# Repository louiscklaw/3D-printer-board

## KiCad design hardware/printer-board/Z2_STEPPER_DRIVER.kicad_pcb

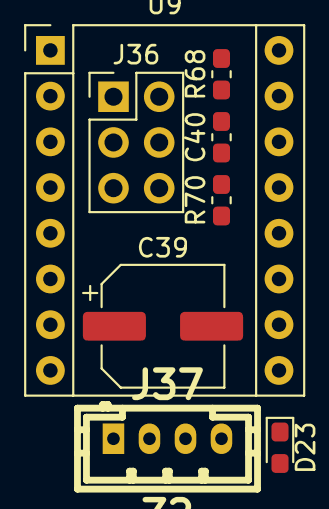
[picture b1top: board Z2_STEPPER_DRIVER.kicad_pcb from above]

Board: 2 copper layers, 9 parts (1 on the bottom side), 13 nets, no tracks yet.

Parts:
C39: CP100uf,25V; CP_Elec_6.3x7.7
C40: C104,0603; C_0603_1608Metric_Pad1.05x0.95mm_HandSolder
D23: LED_BLUE,0603; LED_0603_1608Metric_Pad1.05x0.95mm_HandSolder
J36: MS_SELECT; PinHeader_2x03_P2.54mm_Vertical
J37: Z2; b4b-ph-kl,stepper_terminal
R68: R104,0603; R_0603_1608Metric_Pad1.05x0.95mm_HandSolder
R69: R102,0603; R_0603_1608Metric_Pad1.05x0.95mm_HandSolder
R70: R103,0603; R_0603_1608Metric_Pad1.05x0.95mm_HandSolder
U9: A4988_MODULE; Pololu_Breakout-16_15.2x20.3mm

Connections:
+3V3_STM32: C40.2, J36.2, J36.4, J36.6, R69.1, R70.1, U9.10
+12V: C39.1, U9.16
/~Z2_EN~: D23.1, R70.2, U9.1
GND: C39.2, C40.1, R68.1, U9.9, U9.15
unnamed: D23.2, R69.2
unnamed: J36.1, R68.2, U9.2
unnamed: J36.3, U9.3
unnamed: J36.5, U9.4
unnamed: J37.1, U9.14
unnamed: J37.2, U9.13
unnamed: J37.3, U9.12
unnamed: J37.4, U9.11
unnamed: U9.5, U9.6

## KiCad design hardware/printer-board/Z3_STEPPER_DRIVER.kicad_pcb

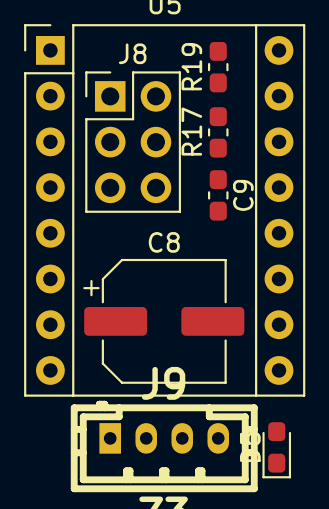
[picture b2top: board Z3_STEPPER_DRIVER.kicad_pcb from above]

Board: 2 copper layers, 9 parts (1 on the bottom side), 13 nets, no tracks yet.

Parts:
C8: CP100uf,25V; CP_Elec_6.3x7.7
C9: C104,0603; C_0603_1608Metric_Pad1.05x0.95mm_HandSolder
D5: LED_BLUE,0603; LED_0603_1608Metric_Pad1.05x0.95mm_HandSolder
J8: MS_SELECT; PinHeader_2x03_P2.54mm_Vertical
J9: Z3; b4b-ph-kl,stepper_terminal
R17: R104,0603; R_0603_1608Metric_Pad1.05x0.95mm_HandSolder
R18: R102,0603; R_0603_1608Metric_Pad1.05x0.95mm_HandSolder
R19: R103,0603; R_0603_1608Metric_Pad1.05x0.95mm_HandSolder
U5: A4988_MODULE; Pololu_Breakout-16_15.2x20.3mm

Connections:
+3V3: C9.2, J8.2, J8.4, J8.6, R18.1, R19.1, U5.10
+12V: C8.1, U5.16
/Z3_~E1_STEP~PER_DRIVER/~Z3_EN~: D5.1, R19.2, U5.1
GND: C8.2, C9.1, R17.1, U5.9, U5.15
unnamed: D5.2, R18.2
unnamed: J8.1, R17.2, U5.2
unnamed: J8.3, U5.3
unnamed: J8.5, U5.4
unnamed: J9.1, U5.14
unnamed: J9.2, U5.13
unnamed: J9.3, U5.12
unnamed: J9.4, U5.11
unnamed: U5.5, U5.6

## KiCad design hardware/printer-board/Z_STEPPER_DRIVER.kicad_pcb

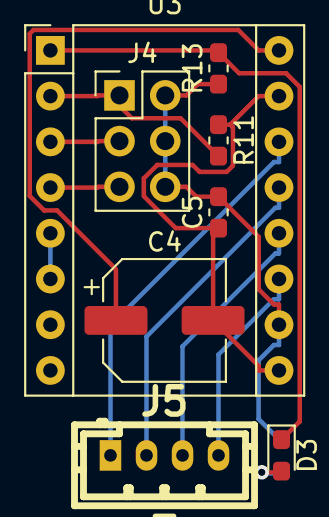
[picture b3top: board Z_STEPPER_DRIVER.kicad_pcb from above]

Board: 2 copper layers, 9 parts (1 on the bottom side), 13 nets.

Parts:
C4: CP100uf,25V; CP_Elec_6.3x7.7
C5: C104,0603; C_0603_1608Metric_Pad1.05x0.95mm_HandSolder
D3: LED_BLUE,0603; LED_0603_1608Metric_Pad1.05x0.95mm_HandSolder
J4: MS_SELECT; PinHeader_2x03_P2.54mm_Vertical
J5: Z; b4b-ph-kl,stepper_terminal
R11: R104,0603; R_0603_1608Metric_Pad1.05x0.95mm_HandSolder
R12: R102,0603; R_0603_1608Metric_Pad1.05x0.95mm_HandSolder
R13: R103,0603; R_0603_1608Metric_Pad1.05x0.95mm_HandSolder
U3: A4988_MODULE; Pololu_Breakout-16_15.2x20.3mm

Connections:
+3V3_STM32: C5.2, J4.2, J4.4, J4.6, R12.1, R13.1, U3.10
+12V: C4.1, U3.16
/~Z_EN~: D3.1, R13.2, U3.1
GND: C4.2, C5.1, R11.1, U3.9, U3.15
unnamed: D3.2, R12.2
unnamed: J4.1, R11.2, U3.2
unnamed: J4.3, U3.3
unnamed: J4.5, U3.4
unnamed: J5.1, U3.14
unnamed: J5.2, U3.13
unnamed: J5.3, U3.12
unnamed: J5.4, U3.11
unnamed: U3.5, U3.6

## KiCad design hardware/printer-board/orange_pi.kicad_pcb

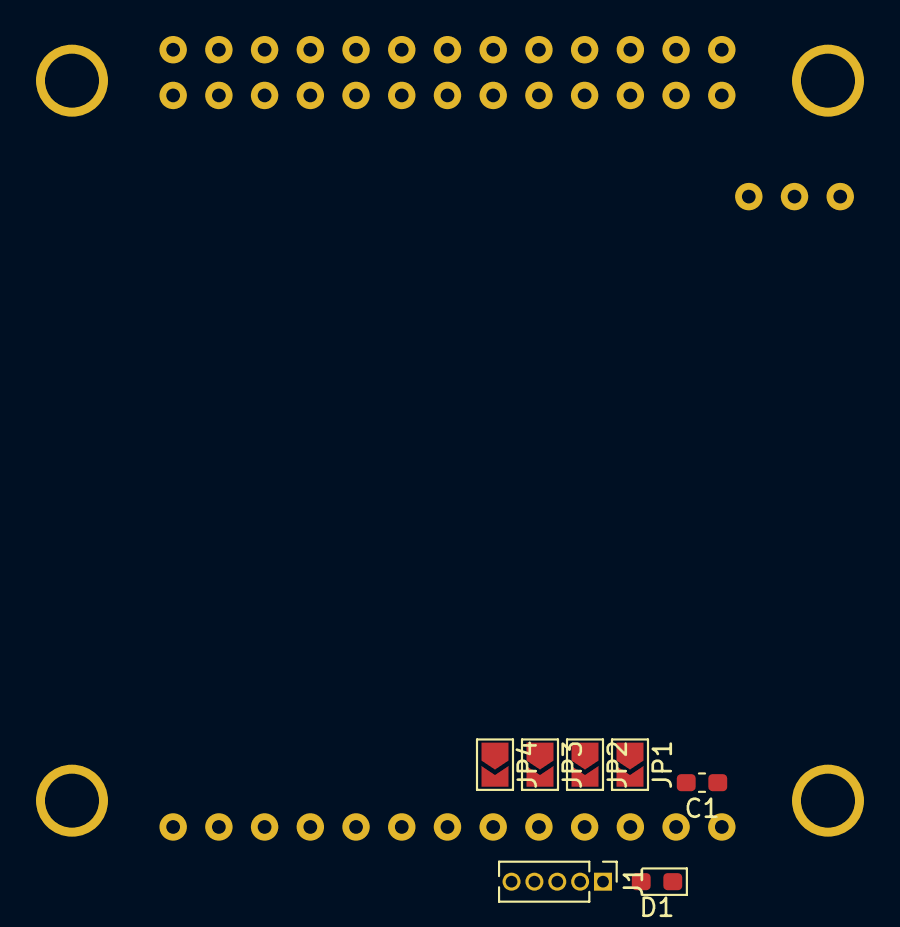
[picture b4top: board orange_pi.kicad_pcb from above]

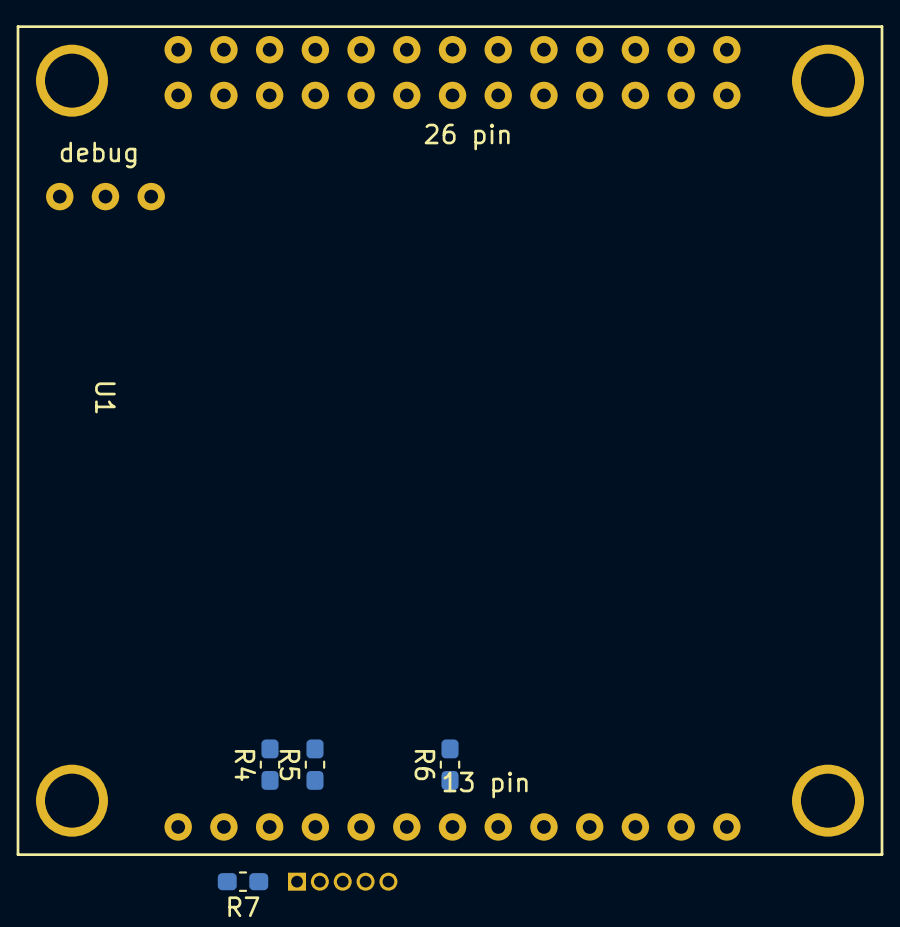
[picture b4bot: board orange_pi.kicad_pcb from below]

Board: 2 copper layers, 12 parts (5 on the bottom side), 9 nets, no tracks yet.

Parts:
C1: CP100uf,35V; C_0603_1608Metric_Pad1.05x0.95mm_HandSolder
D1: 5V HEALTHY; LED_0603_1608Metric_Pad1.05x0.95mm_HandSolder
J1: USB_DEBUG; PinHeader_1x05_P1.27mm_Vertical
JP1, JP2, JP3, JP4: Jumper_NO_Small; SolderJumper-2_P1.3mm_Open_TrianglePad1.0x1.5mm
R4, R5: R220,0603; R_0603_1608Metric_Pad1.05x0.95mm_HandSolder
R6: R152,0603; R_0603_1608Metric_Pad1.05x0.95mm_HandSolder
R7: R102,0603; R_0603_1608Metric_Pad1.05x0.95mm_HandSolder
U1: orange_pi_zero; orangepi-zero

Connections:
+5V_PI_SRC: C1.1, R7.2, U1.1
/USB-DM2: JP1.2, R4.1, U1.3
/USB-DM3: JP3.2, U1.5
/USB-DP2: JP2.2, R5.1, R6.1, U1.4
/USB-DP3: JP4.2, U1.6
GND: C1.2, D1.1, J1.1, U1.2
unnamed: D1.2, R7.1
unnamed: J1.2, R4.2
unnamed: J1.3, R5.2

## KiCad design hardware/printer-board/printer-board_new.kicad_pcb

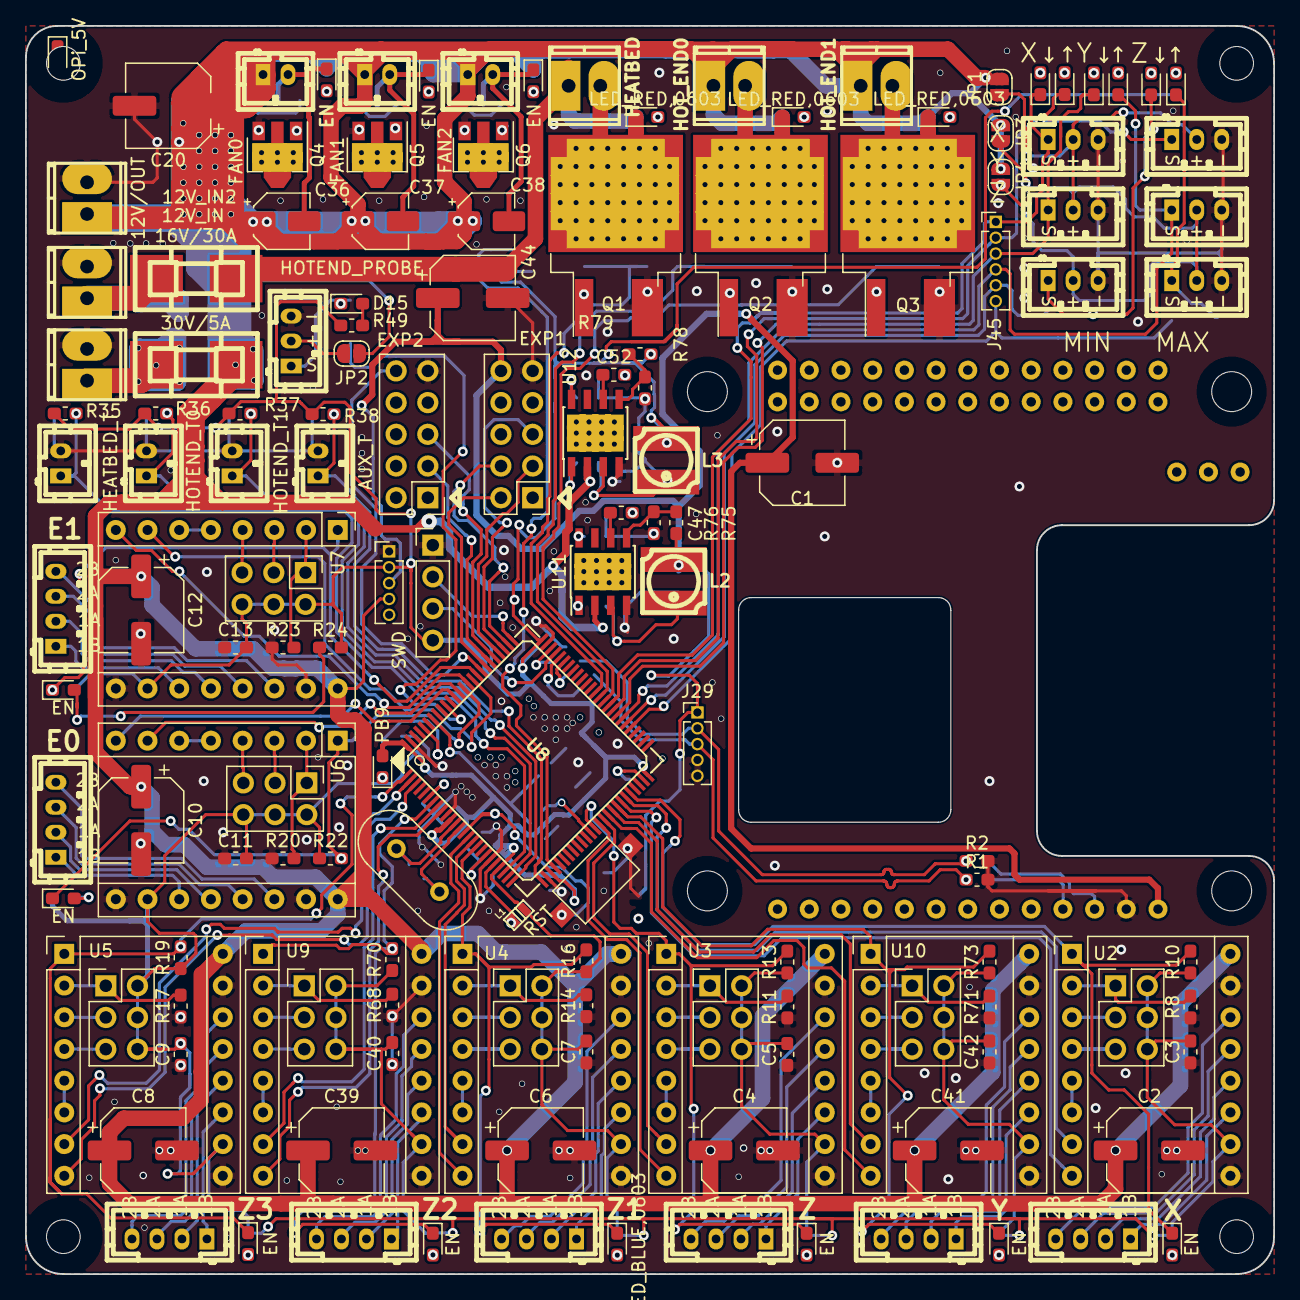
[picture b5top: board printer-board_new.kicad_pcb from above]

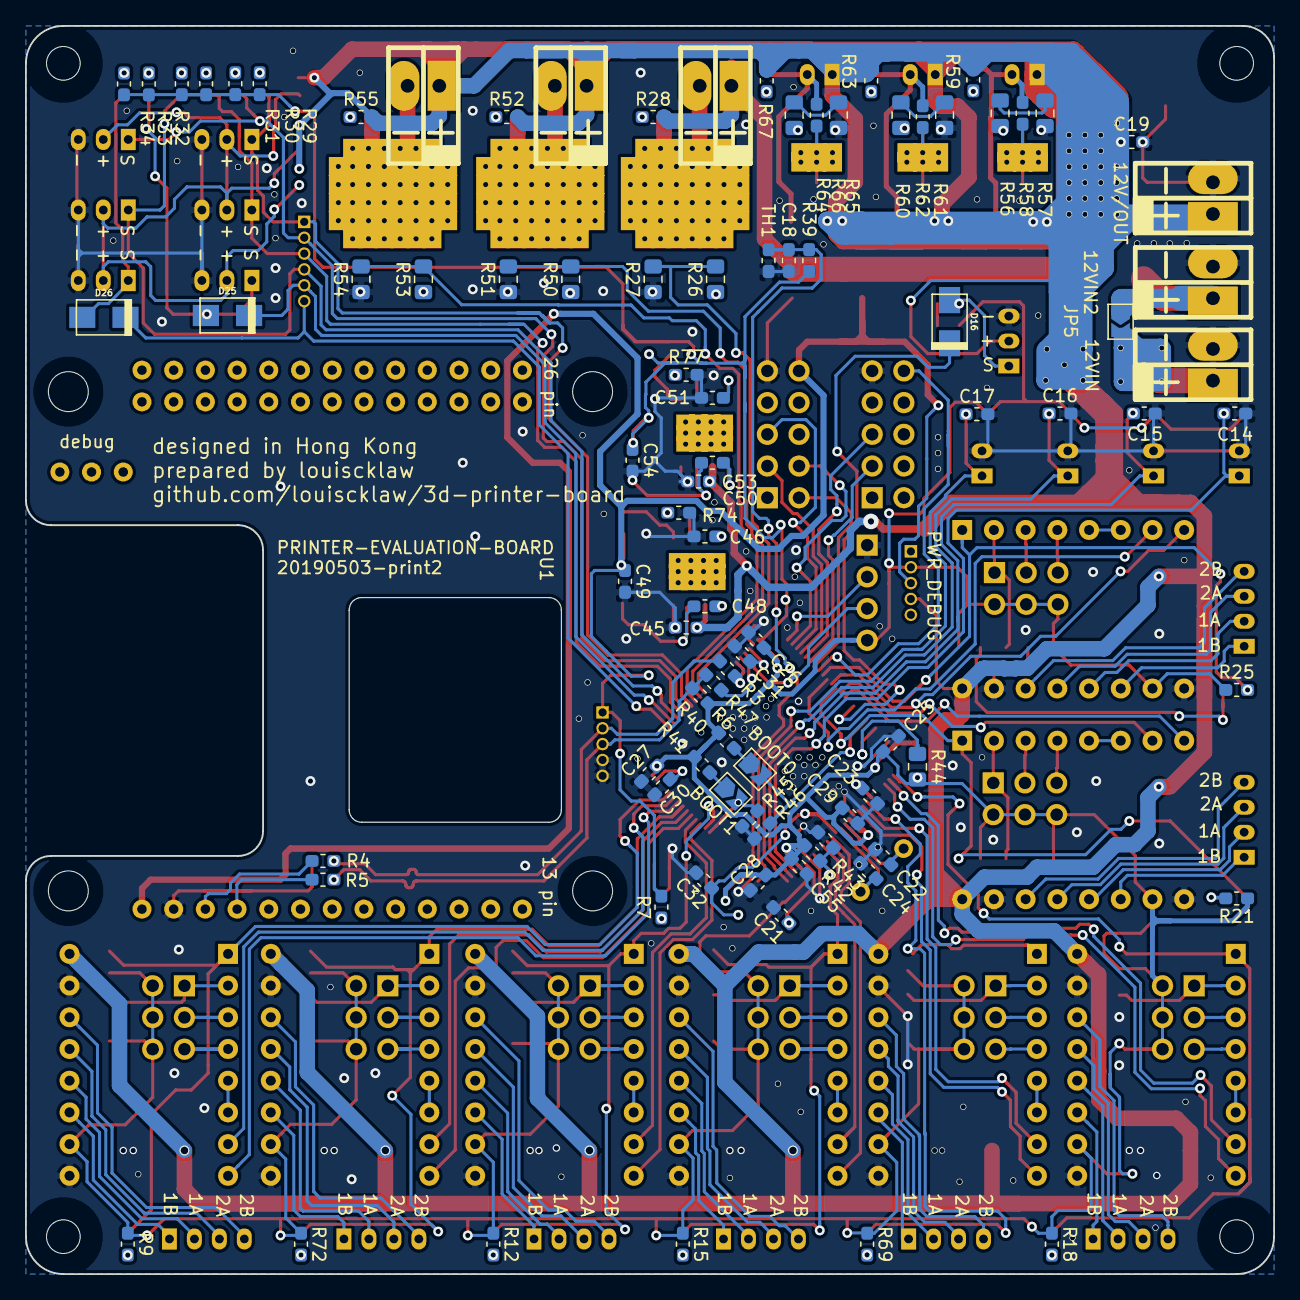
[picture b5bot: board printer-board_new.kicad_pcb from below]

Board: 2 copper layers, 100.0 x 100.0 mm, 234 parts (86 on the bottom side), 198 nets.

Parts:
C1: CP100uf,10V; CP_Elec_6.3x5.3
C2, C4, C6, C8, C10, C12, C39, C41: CP100uf,25V; CP_Elec_6.3x7.7
C3, C5, C7, C9, C11, C13, C19, C21, C23, C25, C26, C27, C28, C30, C31, C32, C40, C42, C46, C51: C104,0603; C_0603_1608Metric_Pad1.05x0.95mm_HandSolder
C14, C15, C16, C17, C18, C45, C50: C106,0603; C_0603_1608Metric_Pad1.05x0.95mm_HandSolder
C20: CP100uf,35V; CP_Elec_6.3x7.7
C22, C24: C10pf,0603; C_0603_1608Metric_Pad1.05x0.95mm_HandSolder
C29, C55: C105,0603; C_0603_1608Metric_Pad1.05x0.95mm_HandSolder
C36, C37, C38: CP1uf,50V; CP_Elec_4x5.3
C44: CP100uf,16V; CP_Elec_6.3x5.3
C47, C52: C332,0603; C_0603_1608Metric_Pad1.05x0.95mm_HandSolder
C48, C53: C103,0603; C_0603_1608Metric_Pad1.05x0.95mm_HandSolder
C49, C54: C226,6.3v,0603; C_0603_1608Metric_Pad1.05x0.95mm_HandSolder
D1: OPi_5V; LED_0603_1608Metric_Pad1.05x0.95mm_HandSolder
D2, D3, D5, D6, D7, D20, D21, D22, D23, D24: EN; LED_0603_1608Metric_Pad1.05x0.95mm_HandSolder
D4, D15: LED_BLUE,0603; LED_0603_1608Metric_Pad1.05x0.95mm_HandSolder
D8, D18, D19: LED_RED,0603; LED_0603_1608Metric_Pad1.05x0.95mm_HandSolder
D9: X↓; LED_0603_1608Metric_Pad1.05x0.95mm_HandSolder
D10, D12, D14: ↑; LED_0603_1608Metric_Pad1.05x0.95mm_HandSolder
D11: Y↓; LED_0603_1608Metric_Pad1.05x0.95mm_HandSolder
D13: Z↓; LED_0603_1608Metric_Pad1.05x0.95mm_HandSolder
D16, D25, D26: SD_1N5817_SS12; do214ac
D17: PB9; LED_0603_1608Metric_Pad1.05x0.95mm_HandSolder
F1: 16V/30A; fuse_smf
F2: 30V/5A; fuse_smf
H1, H2, H3, H4: MOUNT_M3; MountingHole_2.7mm_M2.5,rpi_like
J2, J4, J6, J8, J10, J12, J36, J38: MS_SELECT; PinHeader_2x03_P2.54mm_Vertical
J3: X; b4b-ph-kl,stepper_terminal
J5: Z; b4b-ph-kl,stepper_terminal
J7: Z1; b4b-ph-kl,stepper_terminal
J9: Z3; b4b-ph-kl,stepper_terminal
J11: E0; b4b-ph-kl,stepper_terminal
J13: E1; b4b-ph-kl,stepper_terminal
J14: HEATBED; mpt_0,5%2f2-2,54,heatbed
J15: X_MIN; b3b-ph-kl,end_stop
J16: X_MAX; b3b-ph-kl,end_stop
J17: Y_MIN; b3b-ph-kl,end_stop
J18: Y_MAX; b3b-ph-kl,end_stop
J19: Z_MIN; b3b-ph-kl,end_stop
J20: Z_MAX; b3b-ph-kl,end_stop
J21: HEATBED_T; b2b-ph-kl
J22: HOTEND_T0; b2b-ph-kl
J23: HOTEND_T1; b2b-ph-kl
J24: AUX_T; b2b-ph-kl
J25: 12V_IN2; mpt_0,5%2f2-2,54,12V_SRC
J26: 12V_IN; mpt_0,5%2f2-2,54,12V_SRC
J27: 12V/OUT; mpt_0,5%2f2-2,54,12V_SRC
J28: SWD; PinHeader_1x04_P2.54mm_Vertical
J29: STM32_USB_DEBUG; PinHeader_1x05_P1.27mm_Vertical
J30: PWR_DEBUG; PinHeader_1x05_P1.27mm_Vertical
J31: HOT_END0; mpt_0,5%2f2-2,54,heatbed
J32: HOT_END1; mpt_0,5%2f2-2,54,heatbed
J33: FAN0; b2b-ph-kl,fan_pwm_out
J34: FAN1; b2b-ph-kl,fan_pwm_out
J35: FAN2; b2b-ph-kl,fan_pwm_out
J37: Z2; b4b-ph-kl,stepper_terminal
J39: Y; b4b-ph-kl,stepper_terminal
J41: EXP1; PinHeader_2x05_P2.54mm_Vertical
J42: EXP2; PinHeader_2x05_P2.54mm_Vertical
J45: END_SWITCH_DEBUG; PinHeader_1x06_P1.27mm_Vertical
J48: HOTEND_PROBE; b3b-ph-kl,end_stop
JP1, JP2, JP3, JP4: SolderJumper_2_Open; SolderJumper-2_P1.3mm_Open_RoundedPad1.0x1.5mm
JP5: 12V_JUMPER; SolderJumper-2_P1.3mm_Open_TrianglePad1.0x1.5mm
JP6: BOOT0; SolderJumper-2_P1.3mm_Open_TrianglePad1.0x1.5mm
JP7: BOOT1; SolderJumper-2_P1.3mm_Open_TrianglePad1.0x1.5mm
L1: L_Small; inductor_smd_0603
L2, L3: L_15uH; inductor_smd_4.8x2.8mm
Q1: WSK220N04; TO-263-2,thermal_vias
Q2, Q3: STP55NF06; TO-263-2,thermal_vias
Q4, Q5, Q6: D882; SOT-89-3,thermal_vias
R1, R2: R153,0603; R_0603_1608Metric_Pad1.05x0.95mm_HandSolder
R3, R4, R5, R47: R220,0603; R_0603_1608Metric_Pad1.05x0.95mm_HandSolder
R6: R152,0603; R_0603_1608Metric_Pad1.05x0.95mm_HandSolder
R7, R9, R12, R15, R18, R21, R24, R29, R30, R31, R32, R33, R34, R49, R69, R72: R102,0603; R_0603_1608Metric_Pad1.05x0.95mm_HandSolder
R8, R11, R14, R17, R20, R23, R68, R71: R104,0603; R_0603_1608Metric_Pad1.05x0.95mm_HandSolder
R10, R13, R16, R19, R22, R25, R45, R46, R70, R73, R75, R78: R103,0603; R_0603_1608Metric_Pad1.05x0.95mm_HandSolder
R26, R50, R53, R56, R60, R64: R100,0805; R_0805_2012Metric_Pad1.15x1.40mm_HandSolder
R27, R51, R54, R57, R61, R65: R104,0805; R_0805_2012Metric_Pad1.15x1.40mm_HandSolder
R28, R52, R55, R59, R63, R67: R182,0603; R_0603_1608Metric_Pad1.05x0.95mm_HandSolder
R35, R36, R37, R38, R39, R40, R41: R472,0603; R_0603_1608Metric_Pad1.05x0.95mm_HandSolder
R42: R0,0603; C_0603_1608Metric_Pad1.05x0.95mm_HandSolder
R43: R0,0603; R_0603_1608Metric_Pad1.05x0.95mm_HandSolder
R44: R102,0603; R_0805_2012Metric_Pad1.15x1.40mm_HandSolder
R58, R62, R66: R100,0603; R_0603_1608Metric_Pad1.05x0.95mm_HandSolder
R74, R77: R562,0603; R_0603_1608Metric_Pad1.05x0.95mm_HandSolder
R76: R183,0603; R_0603_1608Metric_Pad1.05x0.95mm_HandSolder
R79: R333,0603; R_0603_1608Metric_Pad1.05x0.95mm_HandSolder
SW1: RST; SW_SPST_CK_RS282G05A3
TH1: Thermistor_NTC; R_0603_1608Metric_Pad1.05x0.95mm_HandSolder
U1: orange_pi_zero; orangepi-zero
U2, U3, U4, U5, U6, U7, U9, U10: A4988_MODULE; Pololu_Breakout-16_15.2x20.3mm
U8: STM32F407VET6; TQFP-100
U11, U12: MP2303A_ALT; SOIC-8_3.9x4.9mm_P1.27mm,thermal_via
Y1: O_8M; Crystal_HC49-4H_Vertical

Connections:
+3V3: C3.2, C5.2, C7.2, C9.2, C11.2, C13.2, C25.2, C26.2, C27.2, C28.2, C29.2, C40.2, C42.2, C54.1, C55.2, D17.2, J2.2, J2.4, J2.6, J4.2, J4.4, J4.6, J6.2, J6.4, J6.6, J8.2, J8.4, J8.6, J10.2, J10.4, J10.6, J12.2, J12.4, J12.6, J28.4, J30.2, J36.2, J36.4, J36.6, J38.2, J38.4, J38.6, L1.1, L3.2, R6.2, R9.1, R10.1, R12.1, R13.1, R15.1, R16.1, R18.1, R19.1, R21.1, R22.1, R24.1, R25.1, R29.1, R30.1, R31.1, R32.1, R33.1, R34.1, R35.1, R36.1, R37.1, R38.1, R39.1, R40.2, R41.2, R42.2, R49.1, R69.1, R70.1, R72.1, R73.1, R79.1, U2.10, U3.10, U4.10, U5.10, U6.10, U7.10, U8.11, U8.22, U8.28, U8.50, U8.75, U8.100, U9.10, U10.10
+5V: C1.1, C44.1, C49.1, J29.1, J30.3, J41.10, L2.2, R7.2, R76.1, U1.1
+12V: C2.1, C4.1, C6.1, C8.1, C10.1, C12.1, C19.1, C20.1, C36.1, C37.1, C38.1, C39.1, C41.1, C45.1, C50.1, F2.2, J27.1, J30.4, J31.1, J32.1, J33.1, J34.1, J35.1, JP1.1, JP2.1, JP3.1, JP4.1, R52.2, R55.2, R59.2, R63.2, R67.2, U2.16, U3.16, U4.16, U5.16, U6.16, U7.16, U9.16, U10.16, U11.2, U12.2
+12V2: F1.2, J14.1, R28.2
/FANS/FAN0/FAN0_N: C36.2, D20.1, J33.2, R58.1
/FANS/FAN1/FAN1_N: C37.2, D21.1, J34.2, R62.1
/FANS/FAN2/FAN2_N: C38.2, D22.1, J35.2, R66.1
/HEATBED/-12V2: D8.1, J14.2, Q1.2
/HOTENDS/HOTEND_0/-12V: D18.1, J31.2, Q2.2
/HOTENDS/HOTEND_1/-12V: D19.1, J32.2, Q3.2
/STM32_CORE/STM32_CORE_MCU/BOOT0: JP6.2, R46.1, U8.94
/STM32_CORE/STM32_CORE_MCU/BOOT1: JP7.2, R45.1, U8.37
/STM32_CORE/STM32_CORE_MCU/DM: R3.1, U8.70
/STM32_CORE/STM32_CORE_MCU/DP: R47.1, U8.71
/STM32_CORE/STM32_CORE_MCU/GND-CAP1: C30.1, U8.49
/STM32_CORE/STM32_CORE_MCU/GND-CAP2: C31.1, U8.73
/STM32_CORE/STM32_CORE_MCU/GND-VCC3V3: R42.1, R43.1, U8.19
/STM32_CORE/STM32_CORE_MCU/RESET: C32.1, SW1.2, U8.14
/STM32_CORE/STM32_CORE_MCU/SWCLK: J28.2, U8.76
/STM32_CORE/STM32_CORE_MCU/SWDIO: J28.3, U8.72
/orange_pi/OPI_USB-DM2: J29.2, R2.1, R3.2, R4.2
/orange_pi/OPI_USB-DP2: J29.3, R1.1, R5.2, R6.1, R47.2
/orange_pi/USB-DM2: R4.1, U1.3
/orange_pi/USB-DP2: R5.1, U1.4
GND: C1.2, C2.2, C3.1, C4.2, C5.1, C6.2, C7.1, C8.2, C9.1, C10.2, C11.1, C12.2, C13.1, C14.2, C15.2, C16.2, C17.2, C18.2, C19.2, C20.2, C21.2, C22.2, C23.2, C24.2, C25.1, C26.1, C27.1, C28.1, C29.1, C30.2, C31.2, C32.2, C39.2, C40.1, C41.2, C42.1, C44.2, C45.2, C46.2, C49.2, C50.2, C51.2, C54.2, C55.1, D1.1, J15.3, J16.3, J17.3, J18.3, J19.3, J20.3, J21.2, J22.2, J23.2, J24.2, J25.2, J26.2, J27.2, J28.1, J29.4, J29.5, J30.1, J41.9, J42.9, J48.3, Q1.3, Q2.3, Q3.3, Q4.3, Q5.3, Q6.3, R1.2, R2.2, R8.1, R11.1, R14.1, R17.1, R20.1, R23.1, R27.1, R43.2, R45.2, R46.2, R51.1, R54.1, R57.1, R61.1, R65.1, R68.1, R71.1, R74.2, R75.2, R77.2, R78.2, SW1.1, TH1.2, U1.2, U2.9, U2.15, U3.9, U3.15, U4.9, U4.15, U5.9, U5.15, U6.9, U6.15, U7.9, U7.15, U8.10, U8.20, U8.27, U8.74, U8.99, U9.9, U9.15, U10.9, U10.15, U11.4, U12.4
unnamed: C21.1, L1.2, U8.21
unnamed: C22.1, U8.12, Y1.1
unnamed: C23.1, U8.6
unnamed: C24.1, U8.13, Y1.2
unnamed: C46.1, U11.8
unnamed: C47.1, U11.6
unnamed: C47.2, R74.1
unnamed: C48.1, L2.1, U11.3
unnamed: C48.2, U11.1
unnamed: C51.1, U12.8
unnamed: C52.1, U12.6
unnamed: C52.2, R77.1
unnamed: C53.1, L3.1, U12.3
unnamed: C53.2, U12.1
unnamed: D1.2, R7.1
unnamed: D2.2, R9.2
unnamed: D3.2, R12.2
unnamed: D4.2, R15.2
unnamed: D5.2, R18.2
unnamed: D6.2, R21.2
unnamed: D7.2, R24.2
unnamed: D8.2, R28.1
unnamed: D9.2, R29.2
unnamed: D10.2, R30.2
unnamed: D11.2, R31.2
unnamed: D12.2, R32.2
unnamed: D13.1, D25.1, J19.1
unnamed: D13.2, R33.2
unnamed: D14.1, D26.1, J20.1
unnamed: D14.2, R34.2
unnamed: D15.1, D16.1, J48.1
unnamed: D15.2, R49.2
unnamed: D17.1, R44.2
unnamed: D18.2, R52.1
unnamed: D19.2, R55.1
unnamed: D20.2, R59.1
unnamed: D21.2, R63.1
unnamed: D22.2, R67.1
unnamed: D23.2, R69.2
unnamed: D24.2, R72.2
unnamed: F1.1, J25.1, JP5.1
unnamed: F2.1, J26.1, JP5.2
unnamed: J2.1, R8.2, U2.2
unnamed: J2.3, U2.3
unnamed: J2.5, U2.4
unnamed: J3.1, U2.11
unnamed: J3.2, U2.12
unnamed: J3.3, U2.13
unnamed: J3.4, U2.14
unnamed: J4.1, R11.2, U3.2
unnamed: J4.3, U3.3
unnamed: J4.5, U3.4
unnamed: J5.1, U3.11
unnamed: J5.2, U3.12
unnamed: J5.3, U3.13
unnamed: J5.4, U3.14
unnamed: J6.1, R14.2, U4.2
unnamed: J6.3, U4.3
unnamed: J6.5, U4.4
unnamed: J7.1, U4.11
unnamed: J7.2, U4.12
unnamed: J7.3, U4.13
unnamed: J7.4, U4.14
unnamed: J8.1, R17.2, U5.2
unnamed: J8.3, U5.3
unnamed: J8.5, U5.4
unnamed: J9.1, U5.11
unnamed: J9.2, U5.12
unnamed: J9.3, U5.13
unnamed: J9.4, U5.14
unnamed: J10.1, R20.2, U6.2
unnamed: J10.3, U6.3
unnamed: J10.5, U6.4
unnamed: J11.1, U6.11
unnamed: J11.2, U6.12
unnamed: J11.3, U6.13
unnamed: J11.4, U6.14
unnamed: J12.1, R23.2, U7.2
unnamed: J12.3, U7.3
unnamed: J12.5, U7.4
unnamed: J13.1, U7.11
unnamed: J13.2, U7.12
unnamed: J13.3, U7.13
unnamed: J13.4, U7.14
unnamed: J15.2, J16.2, JP1.2
unnamed: J17.2, J18.2, JP3.2
unnamed: J19.2, J20.2, JP4.2
unnamed: J36.1, R68.2, U9.2
unnamed: J36.3, U9.3
unnamed: J36.5, U9.4
unnamed: J37.1, U9.11
unnamed: J37.2, U9.12
unnamed: J37.3, U9.13
unnamed: J37.4, U9.14
unnamed: J38.1, R71.2, U10.2
unnamed: J38.3, U10.3
unnamed: J38.5, U10.4
unnamed: J39.1, U10.11
unnamed: J39.2, U10.12
unnamed: J39.3, U10.13
unnamed: J39.4, U10.14
unnamed: J48.2, JP2.2
unnamed: JP6.1, R40.1
unnamed: JP7.1, R41.1
unnamed: Q1.1, R26.1
unnamed: Q2.1, R50.1
unnamed: Q3.1, R53.1
unnamed: Q4.1, R56.1
unnamed: Q4.2, R58.2
unnamed: Q5.1, R60.1
unnamed: Q5.2, R62.2
unnamed: Q6.1, R64.1
unnamed: Q6.2, R66.2
unnamed: R75.1, R76.2, U11.5
unnamed: R78.1, R79.2, U12.5
unnamed: U2.5, U2.6
unnamed: U3.5, U3.6
unnamed: U4.5, U4.6
unnamed: U5.5, U5.6
unnamed: U6.5, U6.6
unnamed: U7.5, U7.6
unnamed: U9.5, U9.6
unnamed: U10.5, U10.6
PA0: C14.1, J21.1, R35.2, U8.23
PA1: C15.1, J22.1, R36.2, U8.24
PA2: C16.1, J23.1, R37.2, U8.25
PA3: C17.1, J24.1, R38.2, U8.26
PA4: C18.1, R39.2, TH1.1, U8.29
PA11: R56.2, R57.2
PA12: R60.2, R61.2
PA13: R64.2, R65.2
PA15: J41.4, U8.77
PB3: U6.8, U8.89
PB5: D16.2, U8.91
PB9: R44.1, U8.96
PC0: U4.8, U8.15
PC1: U4.7, U8.16
PC2: D4.1, R16.2, U4.1, U8.17
PC6: R26.2, R27.2, U8.63
PC10: J41.5, U8.78
PC11: J41.3, U8.79
PC12: J42.5, U8.80
PC13: D23.1, R70.2, U8.7, U9.1
PC14: U8.8, U9.7
PC15: U8.9, U9.8
PD0: J42.3, U8.81
PD1: J41.2, U8.82
PD2: J42.10, U8.83
PD3: D7.1, R25.2, U7.1, U8.84
PD4: U7.7, U8.85
PD5: U7.8, U8.86
PD6: D6.1, R22.2, U6.1, U8.87
PD7: U6.7, U8.88
PD8: D26.2, J45.6, U8.55
PD9: D25.2, J45.5, U8.56
PD10: D12.1, J18.1, J45.4, U8.57
PD11: D11.1, J17.1, J45.3, U8.58
PD12: D10.1, J16.1, J45.2, U8.59
PD13: D9.1, J15.1, J45.1, U8.60
PD14: R53.2, R54.2, U8.61
PD15: R50.2, R51.2, U8.62
PE2: D5.1, R19.2, U5.1, U8.1
PE3: U5.7, U8.2
PE4: U5.8, U8.3
PE7: D3.1, R13.2, U3.1, U8.38
PE8: U3.8, U8.39
PE9: U3.7, U8.40
PE10: U8.41, U10.8
PE11: U8.42, U10.7
PE12: D24.1, R73.2, U8.43, U10.1
PE13: U2.8, U8.44
PE14: U2.7, U8.45
PE15: D2.1, R10.2, U2.1, U8.46

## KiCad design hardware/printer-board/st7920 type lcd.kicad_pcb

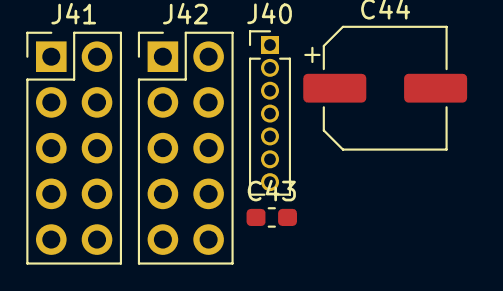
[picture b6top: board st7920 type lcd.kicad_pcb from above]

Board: 2 copper layers, 5 parts (0 on the bottom side), 2 nets, no tracks yet.

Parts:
C43: C104,0603; C_0603_1608Metric_Pad1.05x0.95mm_HandSolder
C44: CP100uf,16V; CP_Elec_6.3x5.3
J40: Conn_01x07; PinHeader_1x07_P1.27mm_Vertical
J41: EXP1; PinHeader_2x05_P2.54mm_Vertical
J42: EXP2; PinHeader_2x05_P2.54mm_Vertical

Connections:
+3V3: C43.1, C44.1, J40.2, J41.10
GND: C43.2, C44.2, J40.1, J41.9, J42.9
